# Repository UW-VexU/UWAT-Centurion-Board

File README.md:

# UWAT-Centurion-Board

KiCad hardware projects for UWAT VEXU.

| Board | Description |
|---|---|
| centurion | Main custom sensor board. STM32G491 with 2 smart port RS-485 links (MAX33071E), I2C mux sensor ports, an SPI IMU connector, USB-C to the Jetson and a UART + CAN FD link to ramBar. Rev A: 4 layers (In1 GND, In2 +3.3V), 103.2 x 62.6 mm, fully routed; ERC, DRC and parity clean, layout audit 0 errors. Ready for fab after the checks in its README's Before ordering list. Non-urgent fixes are deferred to [centurion/REV_B_IMPROVEMENTS.md](centurion/REV_B_IMPROVEMENTS.md). It uses footprints and symbols from `powerJackal/lib`. See [centurion/README.md](centurion/README.md) |
| imuBoard | Centurion IMU board, rev 1.0: a Bosch BMI270 on SPI, which plugs into centurion's J5 with a straight JST GH 8-pin cable. 38 x 24 mm, 2 layers, two #8-32 holes 1 in apart. Routed; ERC, DRC and parity clean. See [imuBoard/README.md](imuBoard/README.md) |
| powerJackal | Smart port power test board, rev A. See [powerJackal/README.md](powerJackal/README.md) |
| stellaNova | VEX V5 wireless debugger. An ESP32-S3 bridges one smart port (RS-485) to WiFi and Bluetooth LE. See [stellaNova/README.md](stellaNova/README.md) |
| rambar | Not in the repo yet |

[PCB_DESIGN_GUIDELINES.md](PCB_DESIGN_GUIDELINES.md) has the layout rules, fab limits (PCBWay and JLCPCB) and a pre-order checklist for all of these boards.

`.claude/agents/` has four Claude Code review agents that work on any KiCad project in this repo: `pcb-footprint-checker` (footprints vs datasheets), `pcb-layout-auditor` (measures the routed copper against the guidelines), `pcb-power-thermal` (rail budget, regulator heat, fuses) and `pcb-signal-checker` (I2C, UART, RS-485, CAN, SPI, USB, clocks, logic levels). They only read files. Ask Claude Code to run one on a board folder, for example "run pcb-layout-auditor on centurion".

## Making Gerber files

These steps work for any board in this repo (KiCad 10). The examples use centurion; for a 2-layer board, leave out In1.Cu and In2.Cu.

### In KiCad

1. Open the board's `.kicad_pcb` in the PCB editor. Run **Inspect → Design Rules Checker** first, with "Refill all zones" ticked. It should show 0 violations and 0 unconnected items.
2. **File → Fabrication Outputs → Gerbers (.gbr)...**
   - **Output directory:** `fab/gerbers/`, inside the board's folder.
   - **Layers:** F.Cu, In1.Cu, In2.Cu, B.Cu, F.Silkscreen, B.Silkscreen, F.Mask, B.Mask, F.Paste, B.Paste, Edge.Cuts.
   - **Tick:**
     - Plot reference designators
     - Check zone fills before plotting
     - Use Protel filename extensions
     - Subtract soldermask from silkscreen
   - Leave everything else at its default, then click **Plot**.
3. In the same dialog, click **Generate Drill Files...**
   - **Format:** Excellon
   - **Units:** millimeters
   - **Zeros:** Decimal format
   - **Drill origin:** Absolute
   - **Holes:** untick "PTH and NPTH in single file", so you get separate PTH and NPTH files
   - **Map file:** Gerber X2
   - Click **Generate Drill File**, then close the dialog.
4. Zip everything in `fab/gerbers/`, keeping the files at the top level of the zip with no folder inside it.

### From a terminal

Run this in the board's folder (for example `centurion/`). On Windows, kicad-cli is at `C:\Program Files\KiCad.0in\kicad-cli.exe`.

```bash
kicad-cli pcb export gerbers --layers "F.Cu,In1.Cu,In2.Cu,B.Cu,F.Silkscreen,B.Silkscreen,F.Mask,B.Mask,F.Paste,B.Paste,Edge.Cuts" --subtract-soldermask --check-zones -o fab/gerbers/ centurion.kicad_pcb
```

```bash
kicad-cli pcb export drill --format excellon --drill-origin absolute --excellon-units mm --excellon-zeros-format decimal --excellon-separate-th --generate-map --map-format gerberx2 -o fab/gerbers/ centurion.kicad_pcb
```

Both commands were checked on centurion on 2026-11-04. They produce 16 files, about 0.8 MB zipped.

For a 4-layer board, the copper files are, in order:

| File | Layer | Centurion |
|---|---|---|
| `.gtl` | Top | Signals |
| `.g1` | Inner 1 | GND plane |
| `.g2` | Inner 2 | +3.3V plane |
| `.gbl` | Bottom | Signals |

The other files:
- `.gto` / `.gbo`: silkscreen
- `.gts` / `.gbs`: solder mask
- `.gtp` / `.gbp`: paste
- `.gm1`: board outline
- `-PTH.drl` / `-NPTH.drl`: drills

Fabs read the layer order from these extensions.

### Checking the files

`tools/gerbcheck.py` reads the Gerber and drill files with its own reader, not KiCad's exporter, and checks them against the board file:
- **Drills:** hole and slot counts per size.
- **Layers:** copper, mask and paste, to 0.08 mm.
- **Netlist:** connectivity rebuilt from the Gerber copper and the plated holes alone, then checked against every pad's net. It reports shorts and opens.

It also draws preview PNGs from the Gerbers. It works for 2- and 4-layer boards. Run it from the repo root, with KiCad's Python:

```bash
"C:\Program Files\KiCad.0in\python.exe" tools/gerbcheck.py centurion/centurion.kicad_pcb centurion/fab/gerbers
```

It ends with `RESULT: PASS` (exit code 0) or `RESULT: FAIL` and the reasons. The previews go to `fab/gerbcheck/`.

On 2026-11-05 it passed centurion rev A (125 nets, 0 shorts, 0 opens) and imuBoard (13 nets). To make sure it catches faults, it was also run on a deliberately broken copy of centurion's files, with one MUX_RST track cut and one via drill deleted. It reported both opens and the missing drill.

It doesn't check the silkscreen beyond drawing it, or how the fab processes the files. Still look at the fab's Gerber viewer and approve their production files.

### Ordering at JLCPCB

On 2026-11-04, five centurion boards cost C$40.39 plus C$37.41 UPS shipping at JLCPCB. At PCBWay they cost US$98.76 with DHL, about C$135–140. So JLCPCB is the first choice. Duties and HST are extra at both.

1. Upload the zip, then check the layer order and the outline size in JLCPCB's Gerber viewer.
2. **Settings:**

   | Setting | Value |
   |---|---|
   | Base material | FR-4 |
   | Layers | 4 (read from the files) |
   | Thickness | 1.6 mm |
   | Color | Green |
   | Silkscreen | White |
   | Material type | FR4 TG135 is fine |
   | Surface finish | ENIG if it's cheap, otherwise HASL lead-free. ENIG pads are flat, which helps the 0.5 mm-pitch MCU and the QFN parts. |
   | Via covering | Tented |
   | Outer copper | 1 oz |
   | Impedance control | None |
   | Mark on PCB | "Remove Mark" or "Specify a location", so the order number doesn't land on a crowded area |
3. **Stackup:** pick **JLC04161H-3313**. Its 0.1 mm prepreg is what centurion's simulations assumed. Their default 7628 stackup, with about 0.2 mm prepreg, also works.
4. **Optional:** "Epoxy filled & capped" via covering covers TI's advice to plug the thermal vias under centurion's U1. Skip it if it costs much.

Centurion's silkscreen text is 0.8 mm tall, under JLCPCB's 1.0 mm minimum, so the labels may print a little soft. The copper isn't affected.

[PCB_DESIGN_GUIDELINES.md](PCB_DESIGN_GUIDELINES.md) has both fabs' limits.

`fab/` isn't git-ignored. Commit the zip you actually sent if you want a record of each order; otherwise regenerate it from the board file.

Other folders:

- `tools`: `gerbcheck.py`, the Gerber checker (see [Checking the files](#checking-the-files)).
- `tinaOnboarding`: electrical onboarding materials.
- `ul_*`, `0955012401` and similar folders: downloaded part libraries.

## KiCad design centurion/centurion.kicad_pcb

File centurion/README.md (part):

# centurion: sensor board, rev A

The main custom board for the UWAT VEXU robots. It sits between the V5 brain and the Jetson. It takes power and RS-485 from two V5 smart ports, reads I2C sensors (encoders, ToF distance sensors, the lift laser) through a mux, reads a turret potentiometer on an ADC pin, and talks to an off-board IMU over SPI. It talks to the Jetson over USB-C, with a UART connector as a backup, and to the ramBar board on the arm over a UART and CAN FD cable.

## Status

The schematic was updated on 2026-11-02 to the decisions below, plus the review fixes of 2026-11-03. The PCB is a fully routed **4-layer** board, 103.2 x 62.6 mm: signals on top and bottom, a solid GND plane on In1 and a +3.3V plane on In2. On 2026-11-04 KiCad 10 shows 0 DRC violations, 0 unconnected items and 0 schematic parity issues, and ERC is clean. The signal, connector, USB hot-plug and crosstalk simulations are in [sim/](sim/README.md). The board still has to go through the [Before ordering](#before-ordering) list (fab DFM check, a 1:1 test-fit, and two part checks with a meter). The old hand-routing guides, [HAND_ROUTING.md](HAND_ROUTING.md) and [CLAUDE_DESKTOP_ROUTING.md](CLAUDE_DESKTOP_ROUTING.md), describe the earlier 2-layer board and are kept only as a record. Non-urgent layout and circuit improvements are deferred to rev B in [REV_B_IMPROVEMENTS.md](REV_B_IMPROVEMENTS.md).

- MCU is now the STM32G491RET6. The ESP32-S3 is gone.
- Each smart port has its own MAX33071E RS-485 transceiver, on its own USART with hardware DE.
- The IMU moved off the board. The ICM-42688-P and the ADXRS453 header are gone, replaced by an SPI header for an IMU breakout.
- Four #8-32 mounting holes (H1 to H4) are in, on the bracket pattern measured from the robot CAD.
- KiCad 10 ERC: 0 errors, 0 warnings (see [How this was checked](#how-this-was-checked)).
- J16's USB-C shield pin is renamed `S1` to `SH` to match KiCad 10's USB4105 footprint. Before this the shield pads had no net, so the USB shell would have floated instead of going to GND.
- The BOM is in [bom/](bom/). On 2026-11-02 four values were changed to parts already on centurion, powerJackal or stellaNova, which removed 4 unique part numbers: R8, R9 and R41 33 Ω to 22 Ω; R40 27k to 22k; R46/R47 22k/33k to 10k/15k (same ratio); LED1/LED2 0805 to the 0603 green LED used for D6. On 2026-11-04, after the design review: R38/R39 (USB D+/D-) 22 Ω to 0 Ω, because the STM32G4's USB pins need no external series resistor; F2 0.35 A to 0.5 A hold, the same part as F3, because 8 or more jacks on 3.3 V would trip 0.35 A. C33 added: a 47 uF 10 V polymer tantalum (KEMET T520B476M010ATE070) on 5V_LDO next to Q1, so plugging in USB can't ring U7's input past its 6.5 V rating (see [sim/](sim/README.md)). Also on 2026-11-04: the ESD clamps U5, U8 to U12 and U17 changed from TPD4E05U06DQAR, which is out of stock at DigiKey CA until February 2027, to TPD4E05U06QDQARQ1, TI's automotive (AEC-Q101) version with the same package, pinout and ratings. The BOM was rebuilt in the powerJackal/stellaNova format, with DigiKey price breaks for every part. Later on 2026-11-04, after the connector simulations: R8, R9 and R41 (IMU SPI) 22 Ω to 100 Ω, the same part as R55, so a 0.3 m IMU cable works at any GPIO speed and 0.5 m at medium or low (see [sim/](sim/README.md#connector-simulations)). That dropped the 22 Ω line from the BOM and adds one 100 Ω resistor to the order (26 instead of 25). The BOM's Cables and tools tab lists what it takes to make the JST GH cables, with its own upload file, [bom/centurion_cables_tools_DigiKey_upload.csv](bom/centurion_cables_tools_DigiKey_upload.csv):
  - GH housings and crimp contacts;
  - JST pre-crimped leads for the ramBar and IMU cables;
  - 28 AWG wire in five colours;
  - an Engineer PA-09 crimper and a 30 AWG stripper.

  It comes to about $500 for three cable sets, with $300 of that being wire. It also has the pin order and wire colour for every jack.

The component plan is [docs/Board_Components.xlsx](docs/Board_Components.xlsx). Where this file and the plan disagree, this file has the later decision.

## Folder map

| Path | What it is |
|---|---|
| `centurion.kicad_pro` | The KiCad project. Open this. It holds the net classes and board rules. |
| `centurion.kicad_pcb` | The board: 4 layers, placed and fully routed. In1 is a solid GND plane, In2 a +3.3V plane, GND poured on top and bottom. |
| `centurion.kicad_dru` | Custom DRC rule (hole clearance, see [PCB layout](#pcb-layout)) |
| `REV_B_IMPROVEMENTS.md` | Non-urgent improvements left out of rev A, from the final layout audit and the simulations |
| `HAND_ROUTING.md` | Record only: the hand-routing to-do list for the earlier 2-layer board. That work was replaced by the 4-layer re-layout. |
| `CLAUDE_DESKTOP_ROUTING.md` | Record only: prompts for having Claude Desktop do that hand routing |
| `sim/` | Signal, connector, USB hot-plug and crosstalk simulations ([sim/README.md](sim/README.md)) |
| `centurion.kicad_sch` | Top sheet. It places the sheets below and wires the RS-485 sheet pins. |
| `power.kicad_sch` | Smart port power input, 5 V buck, 3.3 V LDO, USB-C, battery sense, PGOOD, VBUS sense, test pads |
| `smartport.kicad_sch` | One smart port jack and its MAX33071E. Used twice, as SmartPort_A and SmartPort_B. |
| `mcu.kicad_sch` | STM32G491RET6, decoupling, RESET and BOOT buttons, SWD header, status LEDs, 8 MHz crystal |
| `imu.kicad_sch` | IMU breakout connector (SPI1) and the spare SPI connector (SPI3), both JST-GH |
| `sensors.kicad_sch` | I2C mux and its 8 ports, the pot port, AUX1, the spare I2C header, ESD |
| `usb_jetson.kicad_sch` | Backup 3.3 V UART connector to the Jetson, and the ramBar link (UART, CAN FD transceiver, fused 5 V) |
| `lib/` | Project symbols (now includes MAX33071E), footprints and 3D models. The smart port jack uses the stellaNova footprint with the Molex step model. The TPSM53602 footprint is from powerJackal; KiCad has no model for it, so it gets a plain 5 x 5.5 x 4 mm body. |
| `bom/centurion_revA_BOM.xlsx` | BOM in the same format as powerJackal and stellaNova. It has DigiKey Canada stock and CAD price breaks for every part, read 2026-11-04 (or 2026-10-29/30 for parts shared with those boards). It also has a yellow "boards to build" cell (6), suggested order quantities, a green tip when the next price break is cheaper, and red stock cells. Two columns go past the sibling layout: "On hand" (parts left over from the powerJackal and stellaNova orders, from the "Stock check" sheet) and "Earlier order". Not fitted lines have qty 0; team-stock lines (header strip, shunts) aren't ordered. Tabs: BOM, Price breaks, Stock check, DigiKey upload, Design notes. |
| `bom/centurion_revA_DigiKey_upload.csv` | Upload to DigiKey BOM Manager, with the suggested order quantities. Those are 6 boards plus spares, minus what the powerJackal (2 built) and stellaNova (3 built) orders left over, rounded up to a price break where that costs at most $0.50 more. Lines fully covered by that stock are left out, and so are not-fitted and team-stock lines. To change a quantity, type it in the BOM sheet's yellow "Your order qty" column. Then save the "DigiKey upload" sheet as CSV, deleting its 0-quantity lines first. |
| `docs/Board_Components.xlsx` | Original component plan and open questions |
| `docs/centurion_revA_schematic.pdf` | The schematic as a PDF. Regenerate with `kicad-cli sch export pdf -o docs/centurion_revA_schematic.pdf centurion.kicad_sch` |

The project also uses the UWAT library in `../powerJackal/lib`. Keep the repo folders together.

## Decisions

| Topic | Decision | Notes |
|---|---|---|
| Power | powerJackal's core power section | Already copied and checked pin by pin. PGOOD now goes to the MCU, and the test pads are back. |
| USB power | USB-C alone runs the 3.3 V side. Smart ports alone run everything. Both: the smart ports power the board and USB carries data only. | Automatic, through Q1, D9 and D10 (the powerJackal circuit). The 5 V rail stays off on USB alone. |
| MCU | STM32G491RET6 | Hardware RS-485 DE, newer I2C block, UART FIFOs, CAN FD, USB without a crystal. In stock at DigiKey Canada (558 on 2026-11-02). See [MCU choice](#mcu-choice). |
| RS-485 | One MAX33071EASA+ per smart port, each on its own USART with hardware DE | ±65 V bus fault, ±40 V common mode, ±40 kV HBM ESD, 2 Mbps. Same chip as stellaNova. Replaces last year's plug-in MAX485 modules. |
| Brain link | Two ports, wired the same | Firmware can use port A to read from the brain and port B to write to it, or run both half duplex. No board change either way. |
| Wireless | Allowed, but not on this board | The G491 has no radio. stellaNova on a spare port or the Jetson covers it. |
| Camera | On the Jetson | The STM32 camera option was looked at and dropped: its RAM limits it to about 160 x 120 color or 320 x 240 gray. |
| USB host | Not on this board | The Jetson is the USB host. J15, a spare SPI connector, lets a MAX3421E breakout plug in later. |
| ramBar link | J19, JST-GH 6-pin: 5 V, 3.3 V UART and CAN FD on one cable | ramBar talks to centurion, which passes its data on to the brain. Firmware can use the UART, CAN FD or both. See [ramBar link](#rambar-link-usb_jetson-sheet). |
| IMU | Off-board, on SPI through J5 | The team's own IMU board: a BMI270 with a matching JST GH 8-pin jack, plugged in with a straight cable. See [../imuBoard/README.md](../imuBoard/README.md). The ADXRS453 is dropped. |
| I2C mux | One TCA9548A | 2 encoders, 4 ToF, the lift laser and 1 spare. See [Sensor ports](#sensor-ports). |
| Second I2C bus | AUX1 and the spare I2C header J18 | I2C3 on PC8 and PC9 |
| Turret | Laser on mux channel 2, pot on an ADC pin | The turret turns at most 210°, so no slip ring. A slightly longer cable is fine because the laser has its own mux channel. |
| Sensor connector | JST-GH | Chosen on 2026-11-02 for its latch. Every cable connector is JST-GH: right-angle jacks on the edges, vertical (top entry) inside the board. Qwiic breakouts need a GH-to-Qwiic adapter cable: Qwiic is JST SH (1.0 mm) with pins GND, VCC, SDA, SCL, while these jacks are VCC, SCL, SDA, GND. Cable parts and crimping tools are on the BOM's Cables and tools tab. |
| Reverse polarity | None in v1 | Plan Q7 |
| eFuse | None in v1 | Hot-plug inrush is accepted. Plan Q8. |
| Power budget | Measure it on powerJackal | Plan Q2 |
| Mounting | 4 x #8-32 into the brain mount brackets, 93.92 x 50.80 mm pattern | 4.5 mm non-plated holes. See [Board size and mounting](#board-size-and-mounting). |

### MCU choice

The G491 replaced the planned STM32F446. Both are in stock and cost about the same ($16.59 vs $16.80 CAD at qty 1).

| | STM32G491RET6 | STM32F446RET6 |
|---|---|---|
| RS-485 driver enable in hardware | Yes, on USART2 (PA1) and USART3 (PB14) | No. Firmware toggles a GPIO. |
| UART FIFO | 8 bytes | None |
| I2C | 3, newer block | 4, older block known for lockups |
| SPI | 3 | 4 |
| CAN | 2 x CAN FD | 2 x classic CAN |
| USB | Full speed device, runs from the internal 48 MHz clock | Full speed device and host, needs a crystal |
| Camera interface | No | Yes |
| RAM | 112 KB | 128 KB |
| Speed | 170 MHz | 180 MHz |

Centurion needs 2 I2C buses, 2 SPI, 4 UARTs, 1 CAN FD and about 45 pins, so the G491's 52 I/O pins leave room. The camera goes on the Jetson, so the F446's camera interface isn't needed.

On the 64-pin G491, USART1's only DE pin is PA12, which USB needs. That's why the brain ports use USART2 and USART3, and the Jetson UART uses USART1.

### Board size and mounting

Centurion screws onto the two brain mount brackets (`brainMount-frontSlant-left` and `-right` in the robot CAD) with four #8-32 screws, H1 to H4 on the top sheet. Measured in SolidWorks on 2026-11-02:

| | in | mm |
|---|---|---|
| Hole centres, left to right (between the two brackets) | 3.6976 | 93.92 |
| Hole centres, top to bottom (on one bracket) | 2.000 | 50.80 |
| Bracket hole | 0.175 | 4.45 |
| Board hole, non-plated | 0.177 | 4.50 |

- **Top to bottom is along the bracket's slanted face.** That face is the plane the board sits in, so the board sees exactly 2.000 in. The CAD's X and Y deltas (0.657 in and 1.889 in) are just the slant.
- **Footprint.** `UWAT:MountingHole_4.5mm_8-32` from powerJackal: a 4.5 mm non-plated hole with an 8 mm screw-head keep-out. 4.5 mm is the standard free fit for #8 and slightly larger than the 4.45 mm bracket holes, so small bracket misalignment is fine.
- **Not tied to GND.** The holes have no copper, so the robot frame never connects to the board ground through the screws. Same as powerJackal.
- **Smallest outline.** With the hole centres 4.45 mm from the edges like powerJackal, the board is at least 102.8 x 59.7 mm.

The outline is 103.2 x 62.6 mm, close to the smallest the hole pattern allows. The holes stay on the 93.92 x 50.80 mm pattern.

| | mm | Hole centre to edge |
|---|---|---|
| Width (left to right) | 103.22 | 4.65 left, 4.65 right |
| Height (top to bottom) | 62.6 | 6.15 top, 5.65 bottom |

- **Width.** The hole centres are 4.65 mm from the left and right edges, so the holes' 9.3 mm screw-head keep-outs just fit on the board. The connectors on those edges sit between the holes.
- **Height.** There's 1.5 mm extra at the top and 1 mm at the bottom for routing. The eight top jacks sit between H1 and H2, not above them.
- **History.** On 2026-11-02 the board went from 125 x 69.7 mm, to 113 x 69.7 mm, to 103.2 x 62.6 mm, about 18% less area than the 113 mm version. Moving J18 and J14 to the right edge is what let the top row fit between the holes.
- **No headers on the bottom edge.** Headers and connectors are on the left, right and top edges.

## PCB layout

Four layers, all parts on the top side.

| Layer | Use | Dielectric below it |
|---|---|---|
| F.Cu | Parts and most signals (3.6 m of track), GND pour | 0.1 mm prepreg |
| In1.Cu | Solid GND plane, no tracks | 1.24 mm core |
| In2.Cu | +3.3V plane. 22 slow signals and the USB pair also run here (0.3 m), cutting slots in it. | 0.1 mm prepreg |
| B.Cu | Signals (1.35 m), GND pour, small power fills | |

Every top-layer signal sits 0.1 mm over the solid GND plane, so its return current has an unbroken path. Bottom-layer signals reference the +3.3V plane, which is tied to GND through the decoupling caps. The USB pair is on In2 because J16 is on the left edge while the MCU's USB pins (PA11/PA12) are on its right side, about 60 mm away, and moving it to the top layer didn't fit. That's accepted for rev A at full speed; for rev B, move J16, U13, R38 and R39 next to the MCU (see [sim/README.md](sim/README.md)). Ask the fab for this stackup (1.6 mm, 1 oz outer copper), or their closest standard 4-layer stackup.

| Edge | What's there |
|---|---|
| Top | The 8 mux channels, J6 to J13 (ch0 to ch7), on a 10.6 mm pitch between H1 and H2. Every jack has the same cell behind it: its supply shunt header, then its two pullups. The ESD parts sit between jack pairs. |
| Left | J16 (USB-C) at the top, then the J1 and J2 smart ports, all between H1 and H3 with openings at the edge (same offset as powerJackal; the USB-C shell sticks out 0.575 mm, as GCT's footprint intends). U13 (USB ESD) next to J16, U14 and U15 just inside the smart port jacks. |
| Right | Between H2 and H4, top to bottom: J14 (AUX1), J18 (spare I2C), J17 (pot), all bus 2 / U12. JP1 and JP10 (their supply shunts) stand just inside J14 and J18. J5 (IMU) and J15 (spare SPI) are vertical JST-GH just inside those, with U5 below them. |
| Bottom right | Vertical JST-GH inside the board: J4 (Jetson backup UART) and J19 (ramBar), with the ramBar parts (U16, U17, F4, R53, R54) next to J19. |
| Bottom | No connectors on the edge. The power chain sits in the bottom left, next to the smart ports: the USB power path (D10, Q1), OR diodes, F1, TVS, C1, the buck (U1), then the 3.3 V LDO (U7) under the MCU. |

The board runs left to right from inputs and power, through the MCU, to headers and sensor parts. The MCU sits in the middle with a 3 mm fanout keep-out. Its decoupling caps are just outside the package corners, each with its 3.3 V pad facing its VDD pin. The TCA9548A is above it, under the sensor ports. J3 (SWD, debugging only) is right next to it, then the RESET and BOOT buttons and the status LEDs. The USB pair runs from J16 on the left to PA11/PA12 on the MCU's right side, which is fine at full speed.

**Power stage and crystal.** The buck's input caps (C2, C32, C3) sit in a row right above U1's VIN pins. Its output caps (C4, C5) sit under the VOUT pins, and the feedback divider (R29, R30) sits at the FB pin, which keeps the FB node 3.9 mm long. The crystal Y1 sits next to the MCU's OSC pins, with C22 and C23 right at its pads (OSC traces 7.6 and 5.7 mm).

**Silkscreen.** Connectors and buttons print their name in one label with the reference, right beside the part (`J5 IMU`, `SW1 RESET`, `J19 RAMBAR`...), never under a part body or a screw head. J14 (AUX1) and J18 (spare I2C) had no room on top, so their labels are on the bottom silkscreen, behind the jacks. Every supply shunt header has 3V3 and 5V printed at its two end pins. All text is 0.8 mm tall with a 0.15 mm stroke, and may cross vias because the vias are tented. The test pads are 1.5 mm round pads.

**Net classes and rules** (Board Setup, from `centurion.kicad_pro`):

| Class | Nets | Track |
|---|---|---|
| Power | VIN_OR, VIN_MOD, VPORT A and B, +5V | 0.8 mm |
| USB_Power | VBUS_USB, USB_PWR, 5V_LDO, RAMBAR_5V | 0.5 mm |
| 3V3 | +3.3V, SENS_3V3, SENS_5V, every sensor jack VCC | 0.3 mm. The widest that still enters a 0.5 mm pitch MCU pin with 0.2 mm clearance. |
| Default | Everything else | 0.25 mm |

- Clearance 0.2 mm everywhere. Copper to edge 0.5 mm. Vias 0.6 mm with a 0.3 mm drill.
- Minimum track 0.127 mm (5 mil), only for short neck-downs into fine-pitch pads. After routing, every narrowed power segment is widened back to its class width wherever clearance allows. The narrowest power sections left are short necks at pads: VIN_MOD 0.45 mm and VBUS_USB 0.375 mm.
- Hole clearance is 0.25 mm through `centurion.kicad_dru`. The board-level floor is 0.15 mm only because KiCad's stock GCT USB4105 footprint (J16) puts its outer GND pads 0.19 mm from its own plastic locating holes.

**Copper.** Every net, GND included, is routed as tracks. On top of that, In1 is solid GND, In2 is +3.3V, and GND is poured on the top and bottom layers. The board has 663 vias.
- **Stitching vias:** about every 4 mm, a fence along the board edge, and extra vias wherever the plane had none within 3 mm.
- **Ground-pad vias:** top-side GND pads (decoupling caps, ESD clamps, IC ground pins) have their own via down to the In1 plane.
- **Corners:** every track corner of 90° or sharper was chamfered into two 45° bends on 2026-11-04. The only two left, on U3 pin 32 and D4 pin 2, are inside their own pads.
- **Power-net vias:** every power-net layer change has three vias.
- **Buck module:** short copper fills widen the VIN and 5 V paths right at its pins.
- **Keep-outs:**
  - No bottom-layer tracks under the whole buck stage, or under the crystal and its caps (the pour still fills there).
  - No bottom vias under U1, so its thermal vias land in solid GND (TI).
  - No tracks or vias within 4.5 mm of a mounting-hole centre, where the #8 screw heads sit.

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
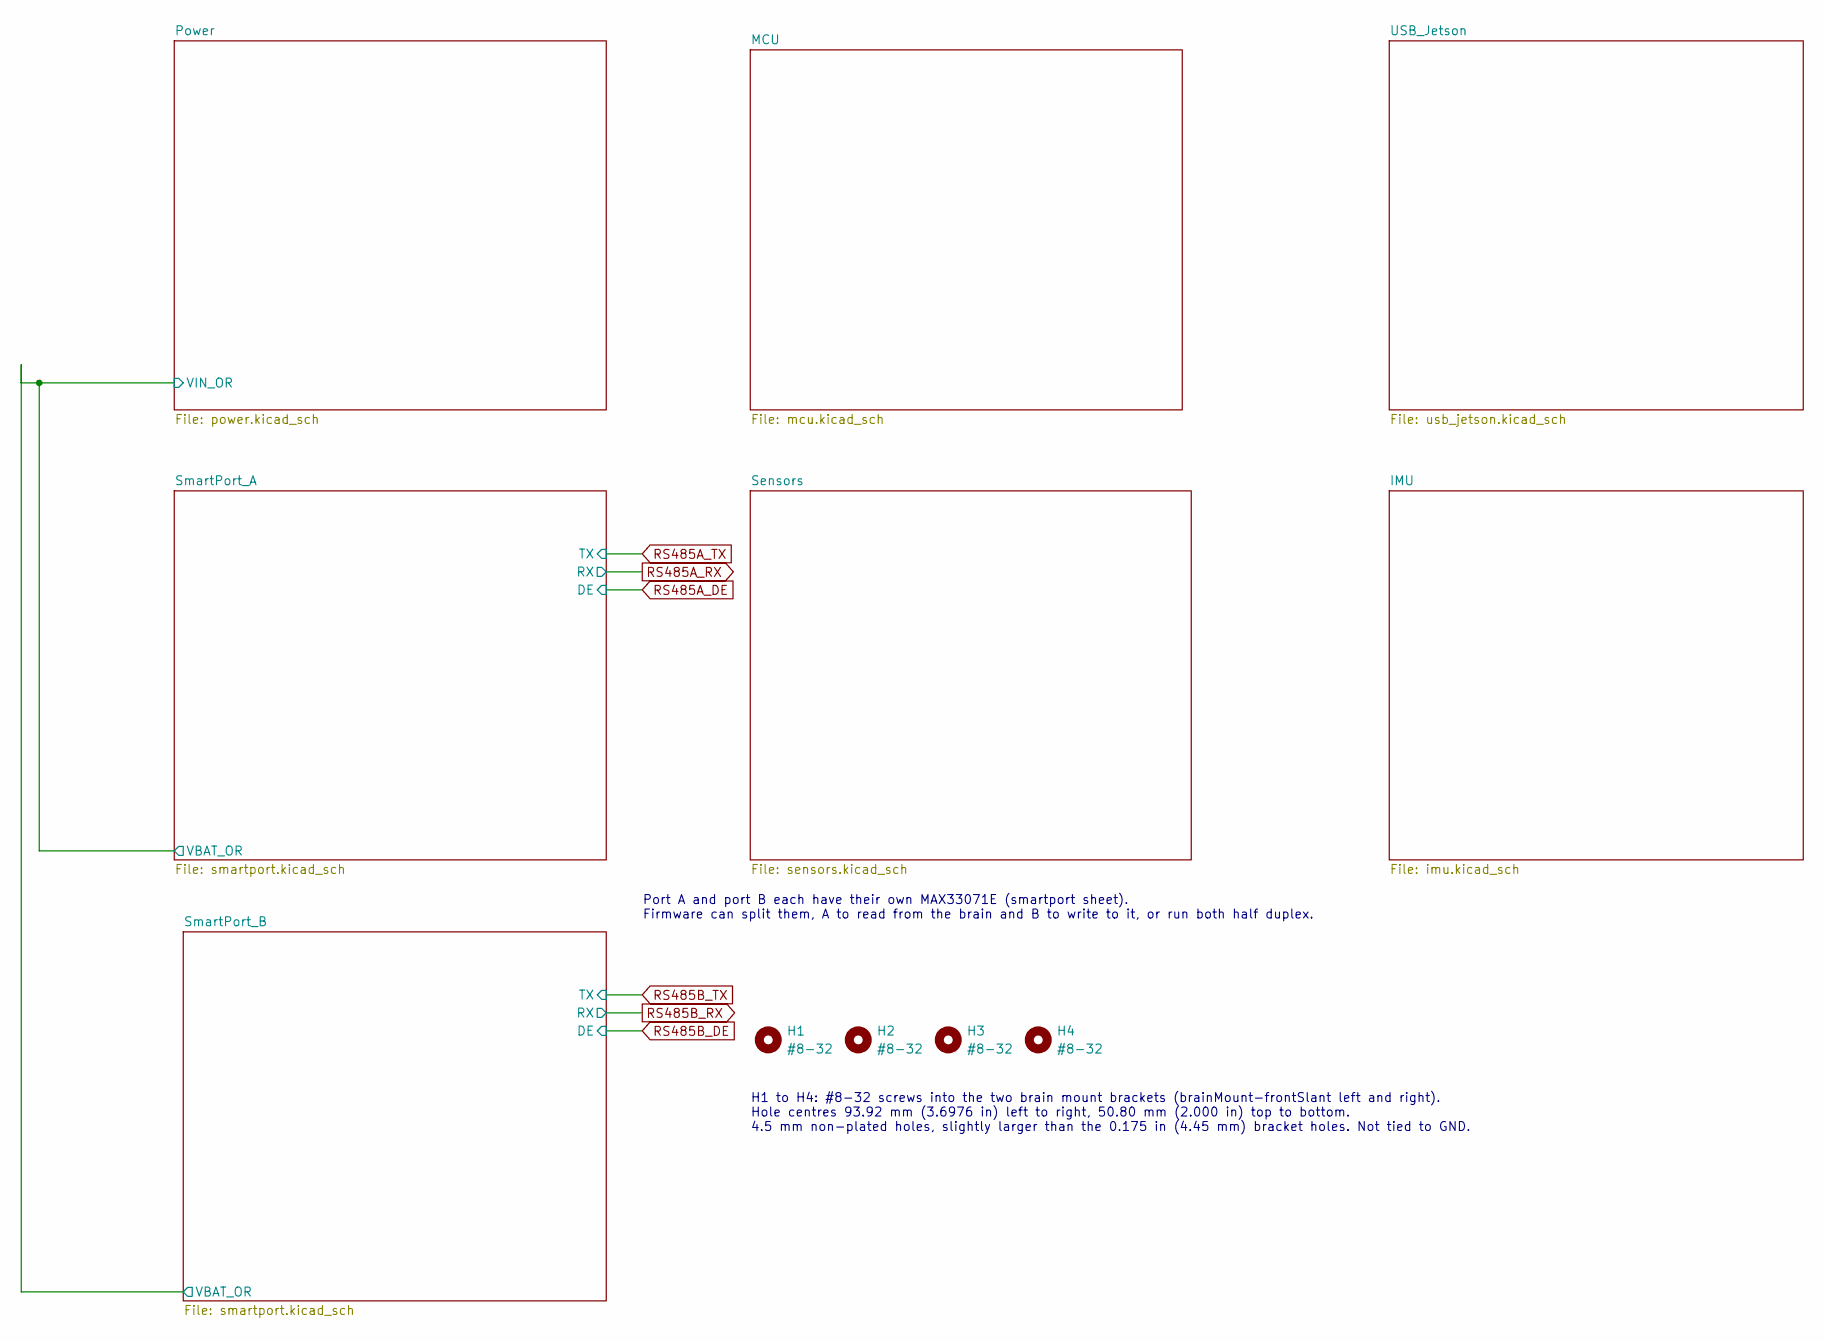
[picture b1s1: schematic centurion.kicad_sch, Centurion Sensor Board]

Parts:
H1, H2, H3, H4: #8-32; MountingHole_4.5mm_8-32

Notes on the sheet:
Port A and port B each have their own MAX33071E (smartport sheet). Firmware can split them, A to read from the brain and B to write to it, or run both half duplex.
H1 to H4: #8-32 screws into the two brain mount brackets (brainMount-frontSlant left and right). Hole centres 93.92 mm (3.6976 in) left to right, 50.80 mm (2.000 in) top to bottom. 4.5 mm non-plated holes, slightly larger than the 0.175 in (4.45 mm) bracket holes. Not tied to GND.

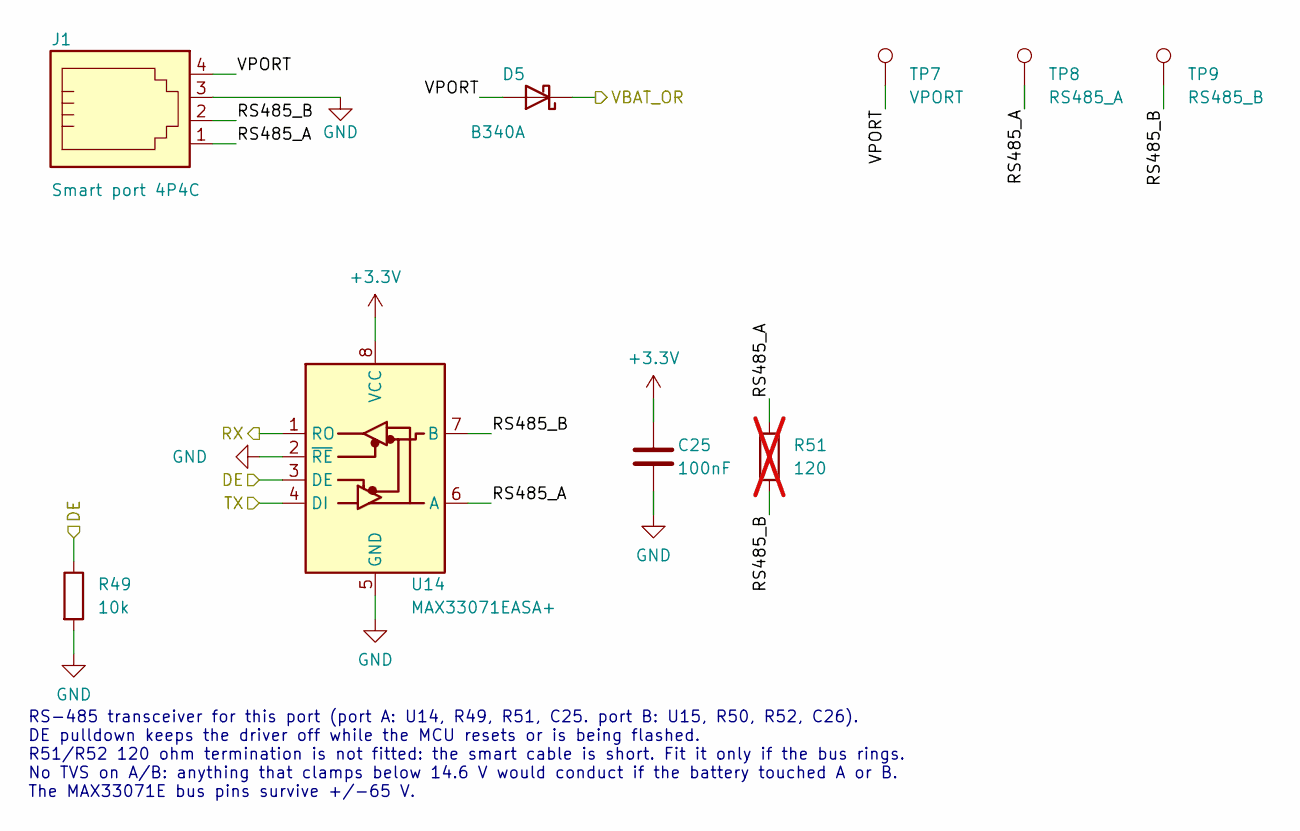
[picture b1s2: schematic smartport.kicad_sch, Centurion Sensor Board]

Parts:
C25: 100nF; C_0805_2012Metric; MPN CC0805KRX7R9BB104
D5: B340A; D_SMA; MPN B340A-13-F
J1: Smart port 4P4C; Molex_95501-2441_4P4C_Horizontal; MPN 0955012441
R49: 10k; R_0805_2012Metric; MPN RC0805FR-0710KL
R51: 120; R_0805_2012Metric; MPN RC0805FR-07120RL; not fitted
TP7: VPORT; TestPoint_Pad_D1.5mm
TP8: RS485_A; TestPoint_Pad_D1.5mm
TP9: RS485_B; TestPoint_Pad_D1.5mm
U14: MAX33071EASA+; SOIC-8_3.9x4.9mm_P1.27mm; MPN MAX33071EASA+

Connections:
+3.3V: C25.1, U14.8 (VCC); also elsewhere on the board
/Power/VIN_OR: D5.1 (K); also elsewhere on the board
/SmartPort_A/RS485_A: J1.1, R51.1, TP8.1, U14.6 (A)
/SmartPort_A/RS485_B: J1.2, R51.2, TP9.1, U14.7 (B)
/SmartPort_A/VPORT: D5.2 (A), J1.4, TP7.1
GND: C25.2, J1.3, R49.2, U14.2 (~RE), U14.5 (GND); also elsewhere on the board
RS485A_DE: R49.1, U14.3 (DE); also elsewhere on the board
RS485A_RX: U14.1 (RO); also elsewhere on the board
RS485A_TX: U14.4 (DI); also elsewhere on the board

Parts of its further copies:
C26: 100nF; C_0805_2012Metric; MPN CC0805KRX7R9BB104
D11: B340A; D_SMA; MPN B340A-13-F
J2: Smart port 4P4C; Molex_95501-2441_4P4C_Horizontal; MPN 0955012441
R50: 10k; R_0805_2012Metric; MPN RC0805FR-0710KL
R52: 120; R_0805_2012Metric; MPN RC0805FR-07120RL; not fitted
TP10: VPORT; TestPoint_Pad_D1.5mm
TP11: RS485_A; TestPoint_Pad_D1.5mm
TP12: RS485_B; TestPoint_Pad_D1.5mm
U15: MAX33071EASA+; SOIC-8_3.9x4.9mm_P1.27mm; MPN MAX33071EASA+

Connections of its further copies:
+3.3V: C26.1, U15.8 (VCC); also elsewhere on the board
/Power/VIN_OR: D11.1 (K); also elsewhere on the board
/SmartPort_B/RS485_A: J2.1, R52.1, TP11.1, U15.6 (A)
/SmartPort_B/RS485_B: J2.2, R52.2, TP12.1, U15.7 (B)
/SmartPort_B/VPORT: D11.2 (A), J2.4, TP10.1
GND: C26.2, J2.3, R50.2, U15.2 (~RE), U15.5 (GND); also elsewhere on the board
RS485B_DE: R50.1, U15.3 (DE); also elsewhere on the board
RS485B_RX: U15.1 (RO); also elsewhere on the board
RS485B_TX: U15.4 (DI); also elsewhere on the board

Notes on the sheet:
RS-485 transceiver for this port (port A: U14, R49, R51, C25. port B: U15, R50, R52, C26). DE pulldown keeps the driver off while the MCU resets or is being flashed. R51/R52 120 ohm termination is not fitted: the smart cable is short. Fit it only if the bus rings. No TVS on A/B: anything that clamp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

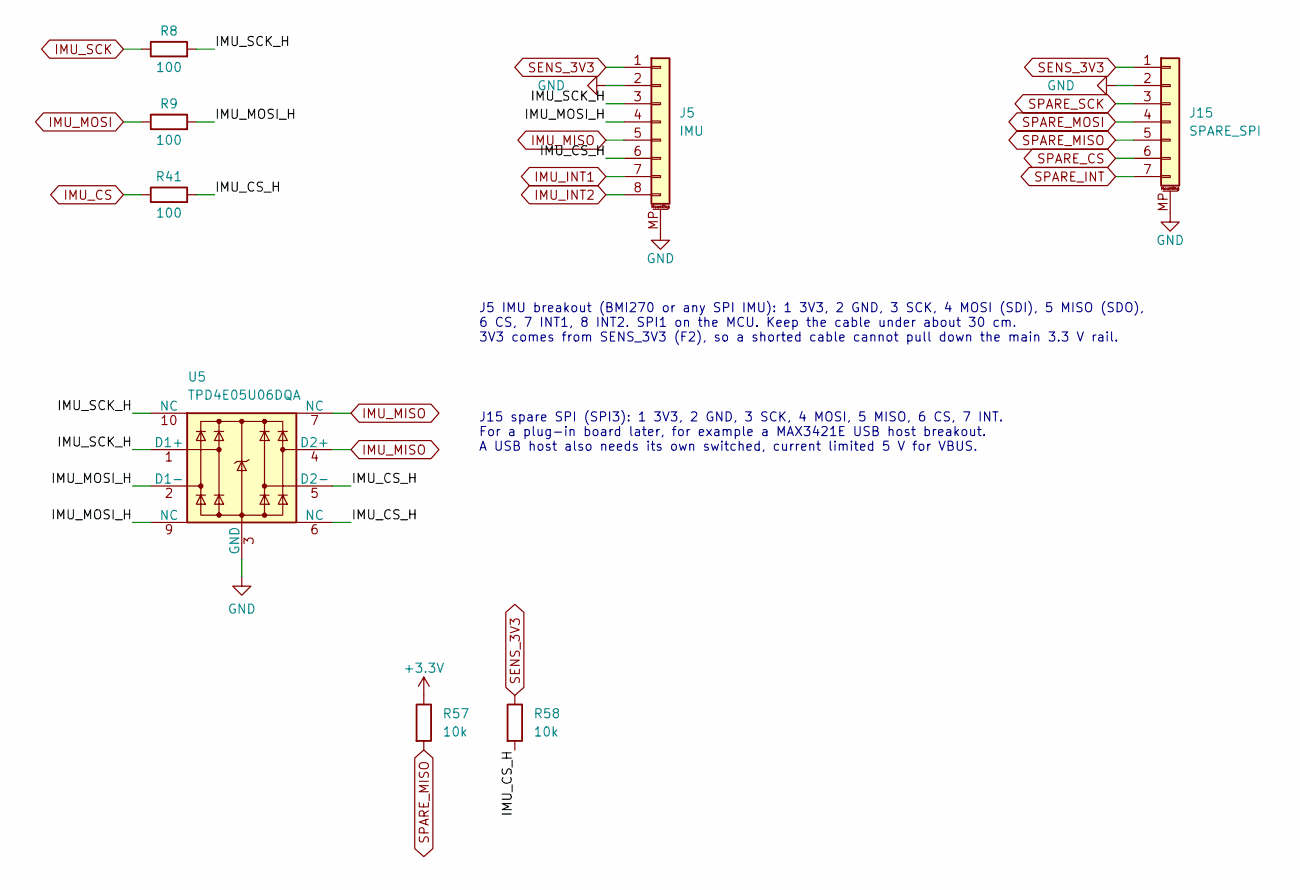
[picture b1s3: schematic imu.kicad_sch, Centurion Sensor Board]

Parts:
J5: IMU; JST_GH_BM08B-GHS-TBT_1x08-1MP_P1.25mm_Vertical; MPN BM08B-GHS-TBT
J15: SPARE_SPI; JST_GH_BM07B-GHS-TBT_1x07-1MP_P1.25mm_Vertical; MPN BM07B-GHS-TBT
R8, R9, R41: 100; R_0805_2012Metric; MPN RC0805FR-07100RL
R57, R58: 10k; R_0805_2012Metric; MPN RC0805FR-0710KL
U5: TPD4E05U06DQA; TI_DQA_USON-10_2.5x1.0mm_P0.5mm; MPN TPD4E05U06QDQARQ1

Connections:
+3.3V: R57.1; also elsewhere on the board
/IMU/IMU_CS_H: J5.6, R41.2, R58.2, U5.5 (D2-), U5.6 (NC)
/IMU/IMU_MOSI_H: J5.4, R9.2, U5.2 (D1-), U5.9 (NC)
/IMU/IMU_SCK_H: J5.3, R8.2, U5.1 (D1+), U5.10 (NC)
GND: J5.2, J5.MP (MountPin), J15.2, J15.MP (MountPin), U5.3 (GND), U5.8 (GND); also elsewhere on the board
IMU_CS: R41.1; also elsewhere on the board
IMU_INT1: J5.7; also elsewhere on the board
IMU_INT2: J5.8; also elsewhere on the board
IMU_MISO: J5.5, U5.4 (D2+), U5.7 (NC); also elsewhere on the board
IMU_MOSI: R9.1; also elsewhere on the board
IMU_SCK: R8.1; also elsewhere on the board
SENS_3V3: J5.1, J15.1, R58.1; also elsewhere on the board
SPARE_CS: J15.6; also elsewhere on the board
SPARE_INT: J15.7; also elsewhere on the board
SPARE_MISO: J15.5, R57.2; also elsewhere on the board
SPARE_MOSI: J15.4; also elsewhere on the board
SPARE_SCK: J15.3; also elsewhere on the board

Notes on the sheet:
J5 IMU breakout (BMI270 or any SPI IMU): 1 3V3, 2 GND, 3 SCK, 4 MOSI (SDI), 5 MISO (SDO), 6 CS, 7 INT1, 8 INT2. SPI1 on the MCU. Keep the cable under about 30 cm. 3V3 comes from SENS_3V3 (F2), so a shorted cable cannot pull down the main 3.3 V rail.
J15 spare SPI (SPI3): 1 3V3, 2 GND, 3 SCK, 4 MOSI, 5 MISO, 6 CS, 7 INT. For a plug-in board later, for example a MAX3421E USB host breakout. A USB host also needs its own switched, current limited 5 V for VBUS.

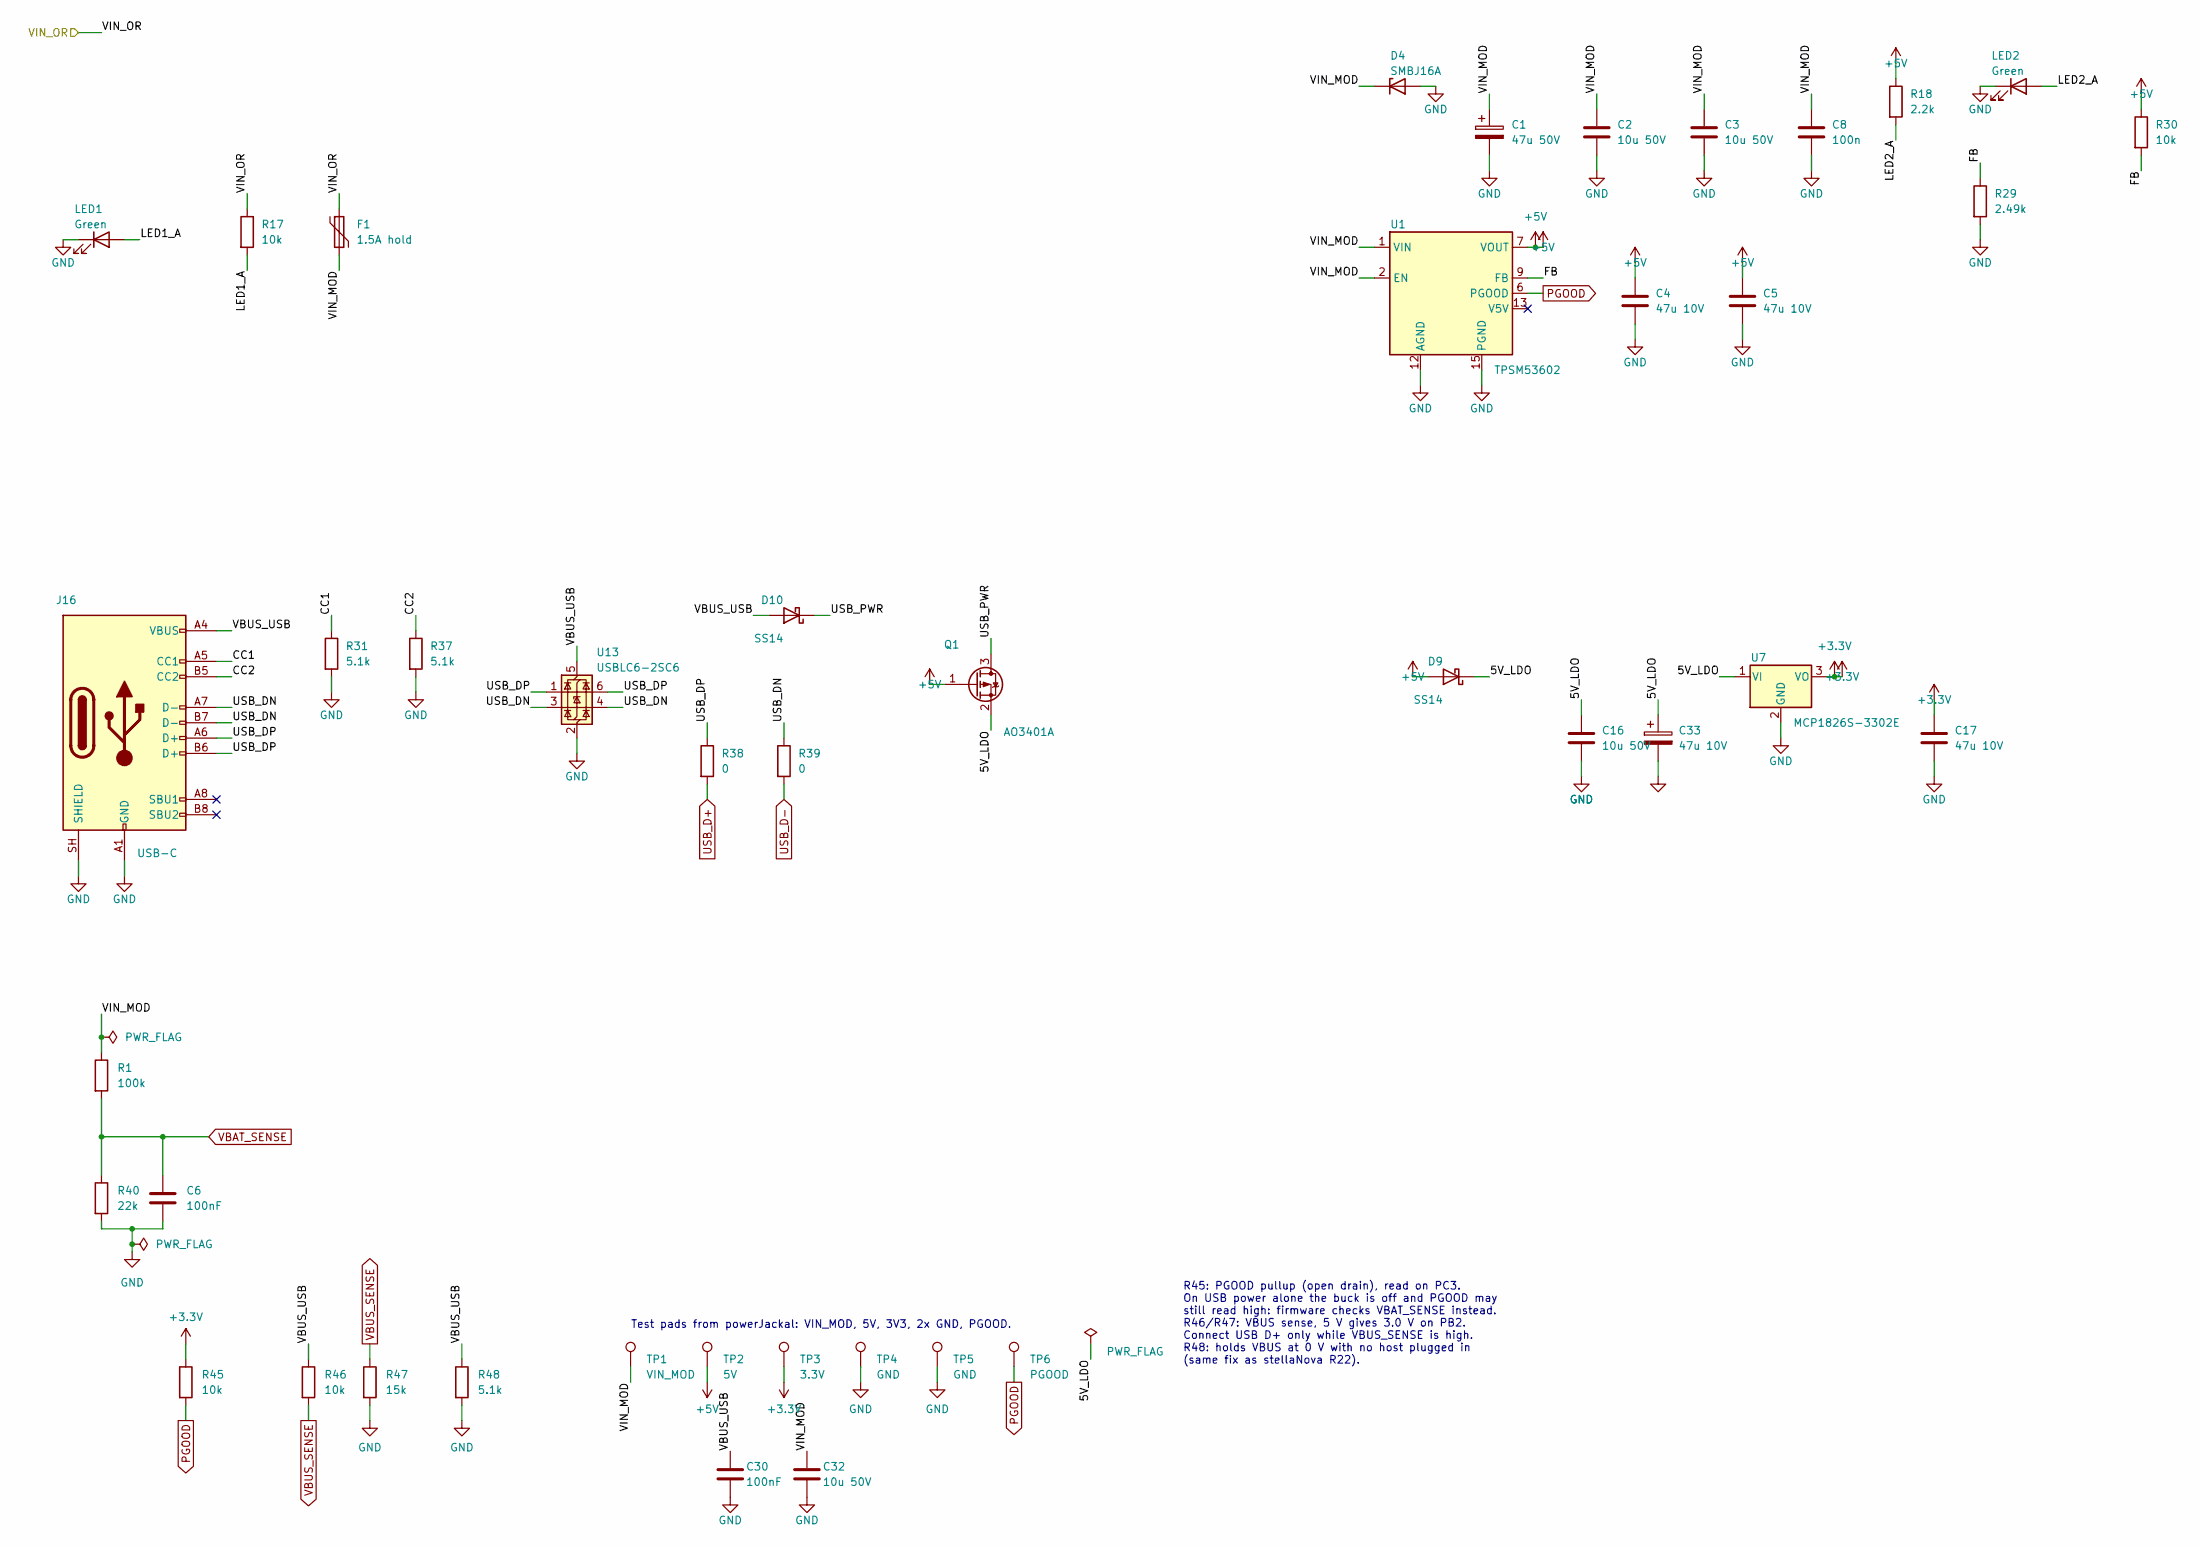
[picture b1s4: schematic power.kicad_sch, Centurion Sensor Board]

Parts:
C1: 47u 50V; CP_Radial_D6.3mm_P2.50mm; MPN EEU-FR1H470
C2, C3, C16, C32: 10u 50V; C_1210_3225Metric; MPN CL32B106KBJNNNE
C4, C5, C17: 47u 10V; C_1206_3216Metric; MPN GRM31CR61A476ME15L
C6, C30: 100nF; C_0805_2012Metric; MPN CC0805KRX7R9BB104
C8: 100n; C_0805_2012Metric; MPN CC0805KRX7R9BB104
C33: 47u 10V; CP_EIA-3528-21_Kemet-B; MPN T520B476M010ATE070
D4: SMBJ16A; D_SMB; MPN SMBJ16A
D9, D10: SS14; D_SMA; MPN SS14-E3/61T
F1: 1.5A hold; Fuse_Littelfuse_2016L; MPN 2016L150/33DR
J16: USB-C; USB_C_Receptacle_GCT_USB4105-xx-A_16P_TopMnt_Horizontal; MPN USB4105-GF-A
LED1, LED2: Green; LED_0603_1608Metric; MPN LTST-C191KGKT
Q1: AO3401A; SOT-23; MPN AO3401A
R1: 100k; R_0805_2012Metric; MPN RC0805FR-07100KL
R17, R30, R45, R46: 10k; R_0805_2012Metric; MPN RC0805FR-0710KL
R18: 2.2k; R_0805_2012Metric; MPN RC0805FR-072K2L
R29: 2.49k; R_0805_2012Metric; MPN RC0805FR-072K49L
R31, R37, R48: 5.1k; R_0805_2012Metric; MPN RMCF0805FT5K10
R38, R39: 0; R_0805_2012Metric; MPN RC0805JR-070RL
R40: 22k; R_0805_2012Metric; MPN RC0805FR-0722KL
R47: 15k; R_0805_2012Metric; MPN RC0805FR-0715KL
TP1: VIN_MOD; TestPoint_Pad_D1.5mm
TP2: 5V; TestPoint_Pad_D1.5mm
TP3: 3.3V; TestPoint_Pad_D1.5mm
TP4, TP5: GND; TestPoint_Pad_D1.5mm
TP6: PGOOD; TestPoint_Pad_D1.5mm
U1: TPSM53602; Texas_B3QFN-14-1EP_5x5.5mm_P0.65mm_ThermalVia; MPN TPSM53602RDAR
U7: MCP1826S-3302E; SOT-223-3_TabPin2; MPN MCP1826ST-3302E/DB
U13: USBLC6-2SC6; SOT-23-6; MPN USBLC6-2SC6

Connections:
+3.3V: C17.1, R45.1, TP3.1, U7.3 (VO); also elsewhere on the board
+5V: C4.1, C5.1, D9.2 (A), Q1.1 (G), R18.1, R30.1, TP2.1, U1.7 (VOUT), U1.8 (VOUT); also elsewhere on the board
/Power/5V_LDO: C16.1, C33.1, D9.1 (K), Q1.2 (S), U7.1 (VI)
/Power/CC1: J16.A5 (CC1), R31.1
/Power/CC2: J16.B5 (CC2), R37.1
/Power/FB: R29.1, R30.2, U1.9 (FB)
/Power/LED1_A: LED1.2 (A), R17.2
/Power/LED2_A: LED2.2 (A), R18.2
/Power/USB_DN: J16.A7 (D-), J16.B7 (D-), R39.1, U13.3 (I/O2), U13.4 (I/O2)
/Power/USB_DP: J16.A6 (D+), J16.B6 (D+), R38.1, U13.1 (I/O1), U13.6 (I/O1)
/Power/USB_PWR: D10.1 (K), Q1.3 (D)
/Power/VBUS_USB: C30.1, D10.2 (A), J16.A4 (VBUS), J16.A9 (VBUS), J16.B4 (VBUS), J16.B9 (VBUS), R46.1, R48.1, U13.5 (VBUS)
/Power/VIN_MOD: C1.1, C2.1, C3.1, C8.1, C32.1, D4.1 (K), F1.2, R1.1, TP1.1, U1.1 (VIN), U1.2 (EN), U1.14 (VIN)
/Power/VIN_OR: F1.1, R17.1; also elsewhere on the board
GND: C1.2, C2.2, C3.2, C4.2, C5.2, C6.2, C8.2, C16.2, C17.2, C30.2, C32.2, C33.2, D4.2 (A), J16.A1 (GND), J16.A12 (GND), J16.B1 (GND), J16.B12 (GND), J16.SH (SHIELD), LED1.1 (K), LED2.1 (K), R29.2, R31.2, R37.2, R40.2, R47.2, R48.2, TP4.1, TP5.1, U1.3 (NC), U1.10 (NC), U1.11 (NC), U1.12 (AGND), U1.15 (PGND), U7.2 (GND), U13.2 (GND); also elsewhere on the board
PGOOD: R45.2, TP6.1, U1.6 (PGOOD); also elsewhere on the board
USB_D+: R38.2; also elsewhere on the board
USB_D-: R39.2; also elsewhere on the board
VBAT_SENSE: C6.1, R1.2, R40.1; also elsewhere on the board
VBUS_SENSE: R46.2, R47.1; also elsewhere on the board

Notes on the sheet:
R45: PGOOD pullup (open drain), read on PC3. On USB power alone the buck is off and PGOOD may still read high: firmware checks VBAT_SENSE instead. R46/R47: VBUS sense, 5 V gives 3.0 V on PB2. Connect USB D+ only while VBUS_SENSE is high. R48: holds VBUS at 0 V with no host plugged in (same fix as s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
Test pads from powerJackal: VIN_MOD, 5V, 3V3, 2x GND, PGOOD.

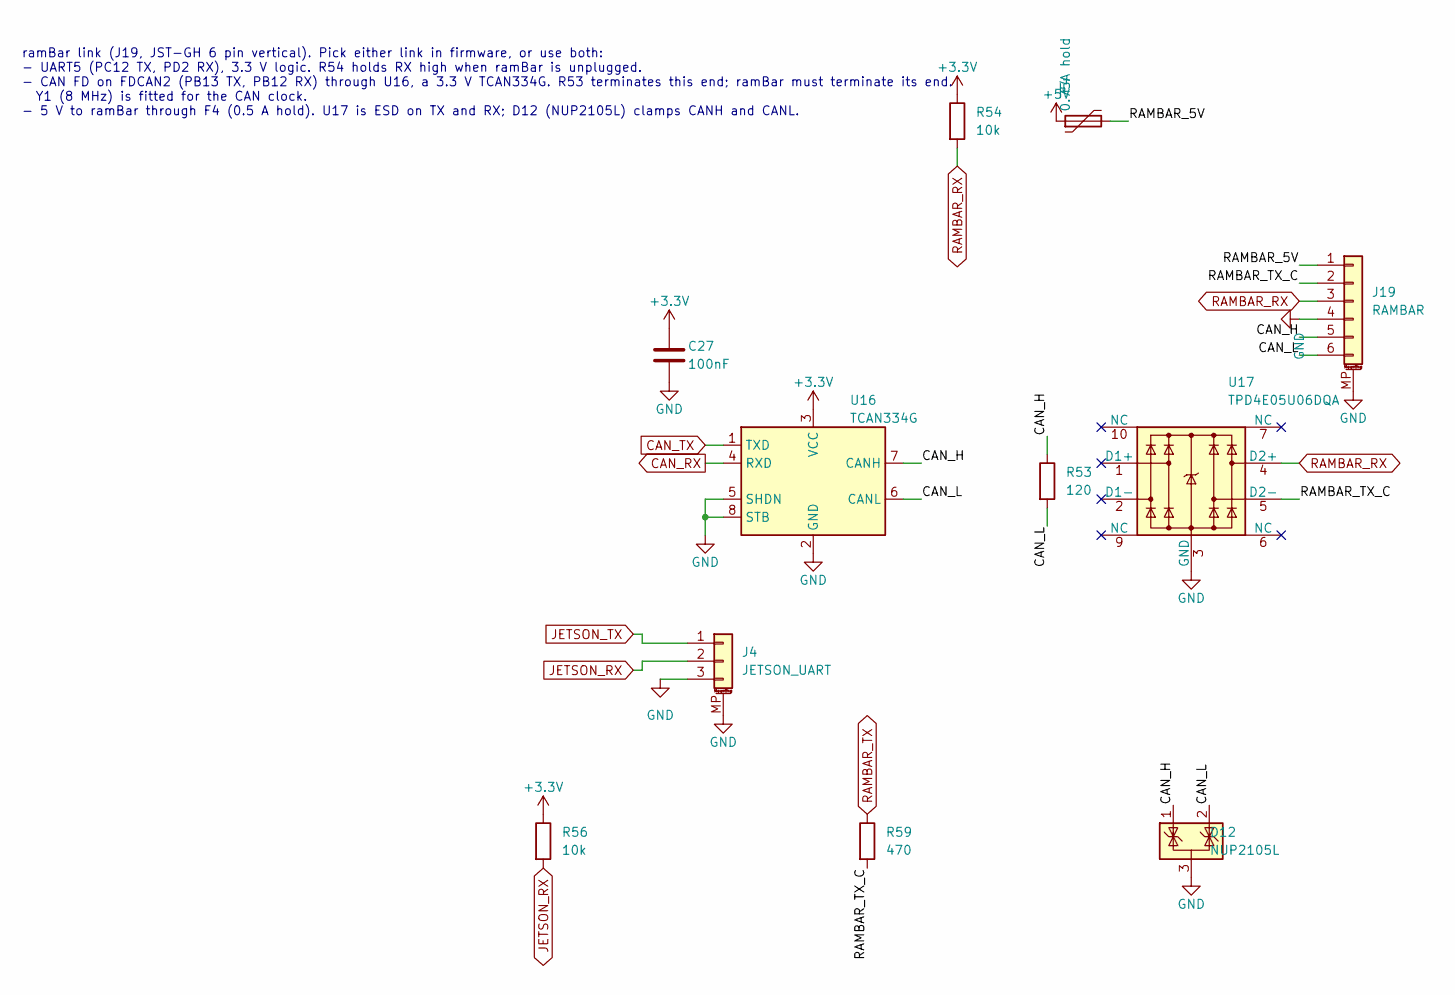
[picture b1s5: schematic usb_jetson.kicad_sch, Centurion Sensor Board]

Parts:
C27: 100nF; C_0805_2012Metric; MPN CC0805KRX7R9BB104
D12: NUP2105L; SOT-23; MPN NUP2105LT1G
F4: 0.75A hold; Fuse_1206_3216Metric; MPN MF-NSMF075-2
J4: JETSON_UART; JST_GH_BM03B-GHS-TBT_1x03-1MP_P1.25mm_Vertical; MPN BM03B-GHS-TBT
J19: RAMBAR; JST_GH_BM06B-GHS-TBT_1x06-1MP_P1.25mm_Vertical; MPN BM06B-GHS-TBT
R53: 120; R_0805_2012Metric; MPN RC0805FR-07120RL
R54, R56: 10k; R_0805_2012Metric; MPN RC0805FR-0710KL
R59: 470; R_0805_2012Metric; MPN RC0805FR-07470RL
U16: TCAN334G; SOIC-8_3.9x4.9mm_P1.27mm; MPN TCAN334GDR
U17: TPD4E05U06DQA; TI_DQA_USON-10_2.5x1.0mm_P0.5mm; MPN TPD4E05U06QDQARQ1

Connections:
+3.3V: C27.1, R54.1, R56.1, U16.3 (VCC); also elsewhere on the board
+5V: F4.1; also elsewhere on the board
/USB_Jetson/CAN_H: D12.1 (K), J19.5, R53.1, U16.7 (CANH)
/USB_Jetson/CAN_L: D12.2 (K), J19.6, R53.2, U16.6 (CANL)
/USB_Jetson/RAMBAR_5V: F4.2, J19.1
/USB_Jetson/RAMBAR_TX_C: J19.2, R59.2, U17.5 (D2-)
CAN_RX: U16.4 (RXD); also elsewhere on the board
CAN_TX: U16.1 (TXD); also elsewhere on the board
GND: C27.2, D12.3 (A), J4.3, J4.MP (MountPin), J19.4, J19.MP (MountPin), U16.2 (GND), U16.5 (SHDN), U16.8 (STB), U17.3 (GND), U17.8 (GND); also elsewhere on the board
JETSON_RX: J4.2, R56.2; also elsewhere on the board
JETSON_TX: J4.1; also elsewhere on the board
RAMBAR_RX: J19.3, R54.2, U17.4 (D2+); also elsewhere on the board
RAMBAR_TX: R59.1; also elsewhere on the board

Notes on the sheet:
ramBar link (J19, JST-GH 6 pin vertical). Pick either link in firmware, or use both: - UART5 (PC12 TX, PD2 RX), 3.3 V logic. R54 holds RX high when ramBar is unplugged. - CAN FD on FDCAN2 (PB13 TX, PB12 RX) through U16, a 3.3 V TCAN334G. R53 terminates this end; ramBar must terminate its end. Y1 (8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
